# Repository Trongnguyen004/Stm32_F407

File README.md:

# Stm32_F407

### #Hình ảnh
<p align="center">
  <table>
    <tr>
      <td>
        
      </td>
      <td>
        
      </td>
    </tr>
  </table>
</p>

### #3D PCB

<p align="center">
  <table>
    <tr>
      <td>
        
      </td>
      <td>
        
      </td>
    </tr>
  </table>
</p>

### #Layout

### #Schematic

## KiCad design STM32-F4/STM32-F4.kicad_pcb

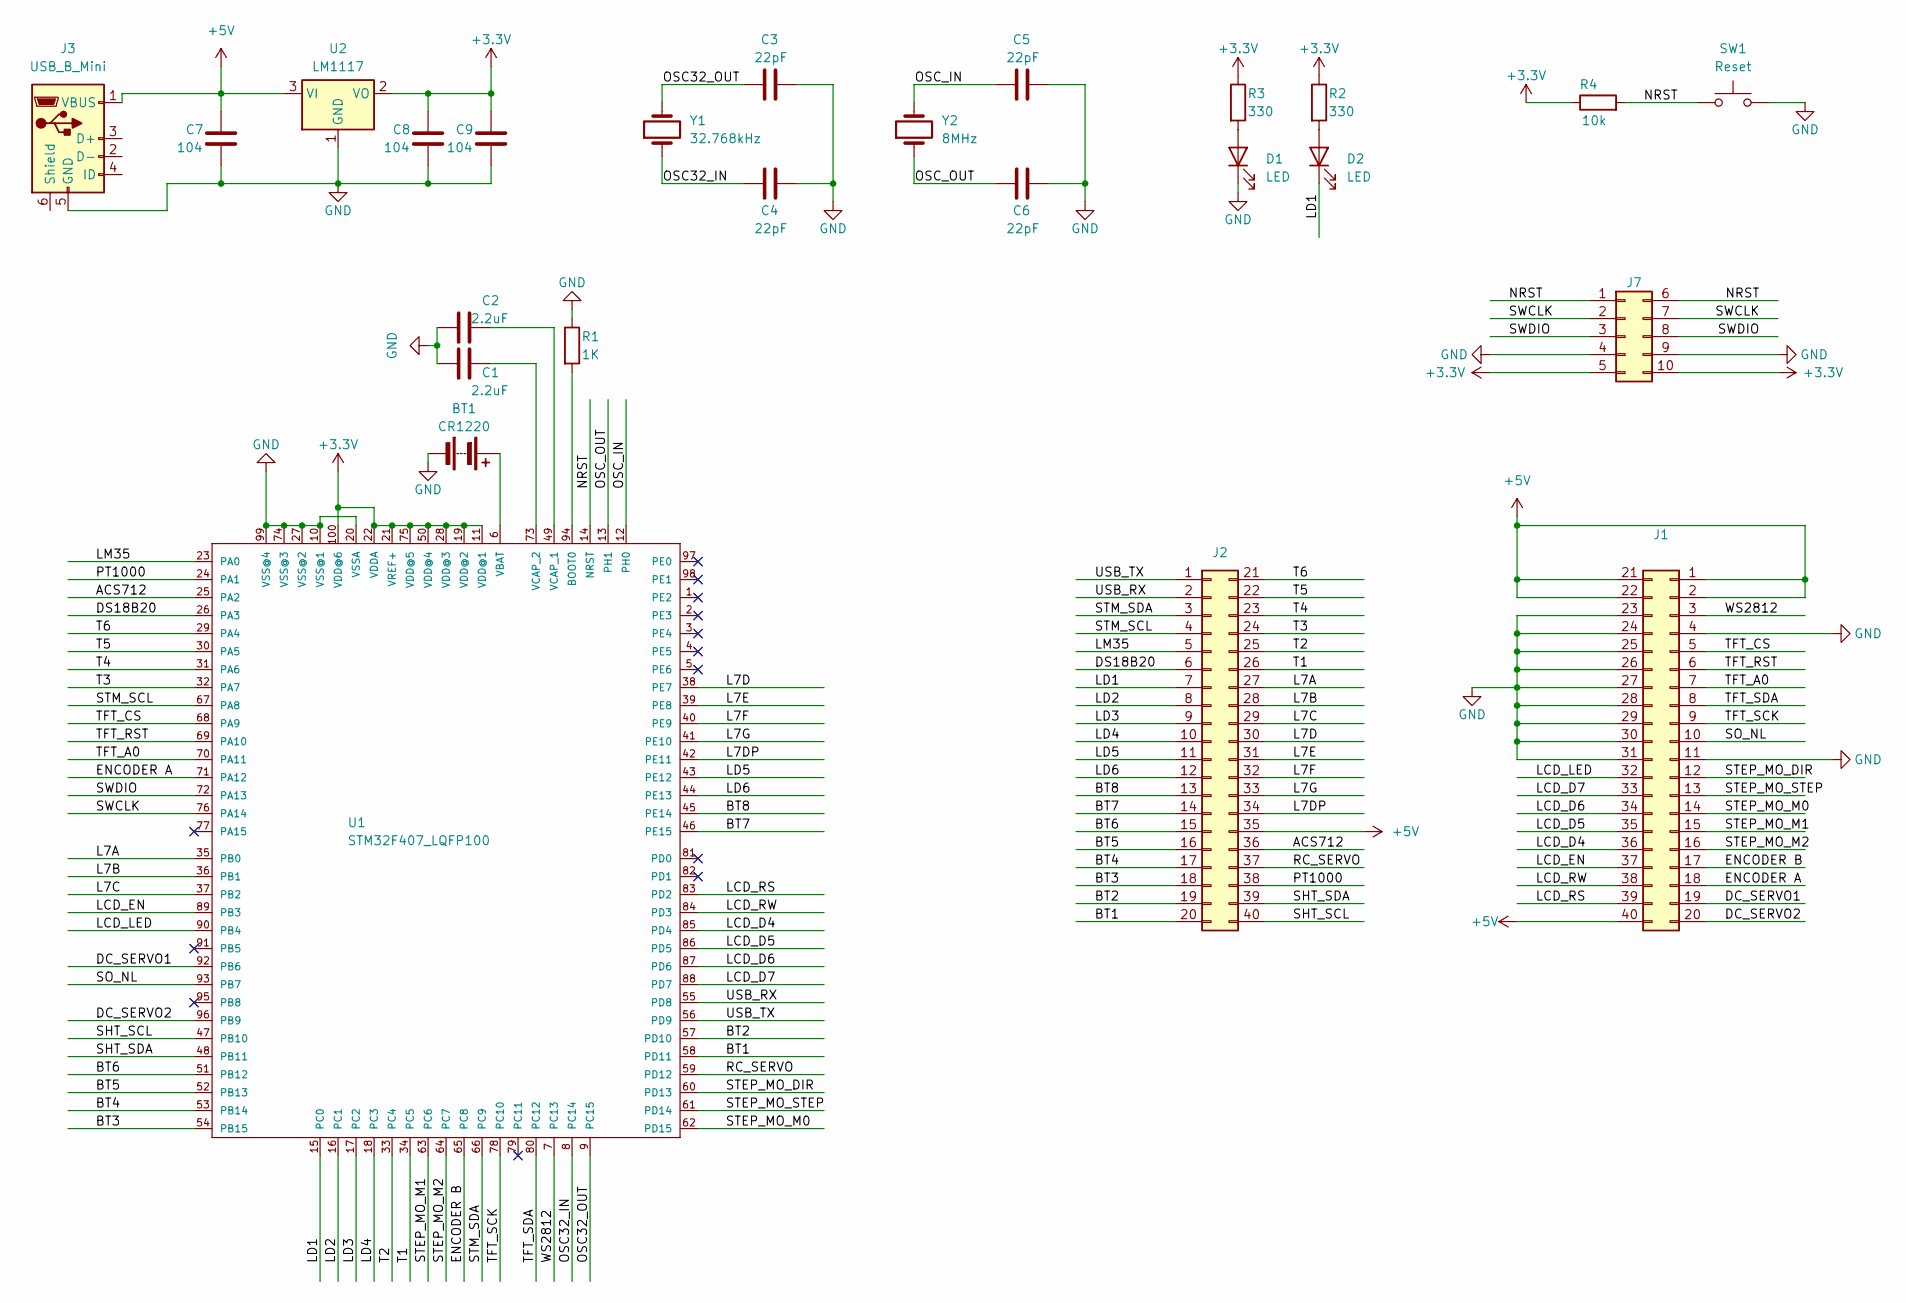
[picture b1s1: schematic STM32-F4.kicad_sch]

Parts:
BT1: CR1220; MPD_BC501SM-TR
C1, C2: 2.2uF; C_0805_2012Metric
C3, C4, C5, C6: 22pF; C_0805_2012Metric
C7, C8, C9: 104; C_0805_2012Metric
D1, D2: LED; LED_0805_2012Metric_Pad1.15x1.40mm_HandSolder
J1, J2: PinHeader_2x20_P2.54mm_Vertical
J3: USB_B_Mini; USB_Mini-B_Wuerth_65100516121_Horizontal
J7: PinHeader_2x05_P2.54mm_Vertical
R1: 1K; R_0805_2012Metric
R2, R3: 330; R_0805_2012Metric
R4: 10k; R_0805_2012Metric
SW1: Reset; SW_PUSH_6mm
U1: STM32F407_LQFP100; LQFP100-0.5-13.8X13.8MM; MPN STM32F407VET6
U2: LM1117; SOT-223-3_TabPin2
Y1: 32.768kHz; XTAL_AB38T-32.768KHZ
Y2: 8MHz; Crystal_HC49-4H_Vertical

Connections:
+3.3V: C8.1, C9.1, J7.5, J7.10, R2.1, R3.1, R4.1, U1.11 (VDD@1), U1.19 (VDD@2), U1.21 (VREF+), U1.22 (VDDA), U1.28 (VDD@3), U1.50 (VDD@4), U1.75 (VDD@5), U1.100 (VDD@6), U2.2 (VO)
+5V: C7.1, J1.1, J1.2, J1.21, J1.22, J1.40, J2.35, J3.1 (VBUS), U2.3 (VI)
/ACS712: J2.36, U1.25 (PA2)
/BT1: J2.20, U1.58 (PD11)
/BT2: J2.19, U1.57 (PD10)
/BT3: J2.18, U1.54 (PB15)
/BT4: J2.17, U1.53 (PB14)
/BT5: J2.16, U1.52 (PB13)
/BT6: J2.15, U1.51 (PB12)
/BT7: J2.14, U1.46 (PE15)
/BT8: J2.13, U1.45 (PE14)
/DC_SERVO1: J1.19, U1.92 (PB6)
/DC_SERVO2: J1.20, U1.96 (PB9)
/DS18B20: J2.6, U1.26 (PA3)
/ENCODER A: J1.18, U1.71 (PA12)
/ENCODER B: J1.17, U1.65 (PC8)
/L7A: J2.27, U1.35 (PB0)
/L7B: J2.28, U1.36 (PB1)
/L7C: J2.29, U1.37 (PB2)
/L7D: J2.30, U1.38 (PE7)
/L7DP: J2.34, U1.42 (PE11)
/L7E: J2.31, U1.39 (PE8)
/L7F: J2.32, U1.40 (PE9)
/L7G: J2.33, U1.41 (PE10)
/LCD_D4: J1.36, U1.85 (PD4)
/LCD_D5: J1.35, U1.86 (PD5)
/LCD_D6: J1.34, U1.87 (PD6)
/LCD_D7: J1.33, U1.88 (PD7)
/LCD_EN: J1.37, U1.89 (PB3)
/LCD_LED: J1.32, U1.90 (PB4)
/LCD_RS: J1.39, U1.83 (PD2)
/LCD_RW: J1.38, U1.84 (PD3)
/LD1: D2.1 (K), J2.7, U1.15 (PC0)
/LD2: J2.8, U1.16 (PC1)
/LD3: J2.9, U1.17 (PC2)
/LD4: J2.10, U1.18 (PC3)
/LD5: J2.11, U1.43 (PE12)
/LD6: J2.12, U1.44 (PE13)
/LM35: J2.5, U1.23 (PA0)
/NRST: J7.1, J7.6, R4.2, SW1.1, U1.14 (NRST)
/OSC32_IN: C4.1, U1.8 (PC14), Y1.1
/OSC32_OUT: C3.1, U1.9 (PC15), Y1.2
/OSC_IN: C5.1, U1.12 (PH0), Y2.2
/OSC_OUT: C6.1, U1.13 (PH1), Y2.1
/PT1000: J2.38, U1.24 (PA1)
/RC_SERVO: J2.37, U1.59 (PD12)
/SHT_SCL: J2.40, U1.47 (PB10)
/SHT_SDA: J2.39, U1.48 (PB11)
/SO_NL: J1.10, U1.93 (PB7)
/STEP_MO_DIR: J1.12, U1.60 (PD13)
/STEP_MO_M0: J1.14, U1.62 (PD15)
/STEP_MO_M1: J1.15, U1.63 (PC6)
/STEP_MO_M2: J1.16, U1.64 (PC7)
/STEP_MO_STEP: J1.13, U1.61 (PD14)
/STM_SCL: J2.4, U1.67 (PA8)
/STM_SDA: J2.3, U1.66 (PC9)
/SWCLK: J7.2, J7.7, U1.76 (PA14)
/SWDIO: J7.3, J7.8, U1.72 (PA13)
/T1: J2.26, U1.34 (PC5)
/T2: J2.25, U1.33 (PC4)
/T3: J2.24, U1.32 (PA7)
/T4: J2.23, U1.31 (PA6)
/T5: J2.22, U1.30 (PA5)
/T6: J2.21, U1.29 (PA4)
/TFT_A0: J1.7, U1.70 (PA11)
/TFT_CS: J1.5, U1.68 (PA9)
/TFT_RST: J1.6, U1.69 (PA10)
/TFT_SCK: J1.9, U1.78 (PC10)
/TFT_SDA: J1.8, U1.80 (PC12)
/USB_RX: J2.2, U1.55 (PD8)
/USB_TX: J2.1, U1.56 (PD9)
/WS2812: J1.3, U1.7 (PC13)
GND: BT1.-, C1.1, C2.1, C3.2, C4.2, C5.2, C6.2, C7.2, C8.2, C9.2, D1.1 (K), J1.4, J1.11, J1.23, J1.24, J1.25, J1.26, J1.27, J1.28, J1.29, J1.30, J1.31, J3.5 (GND), J7.4, J7.9, R1.1, SW1.2, U1.10 (VSS@1), U1.20 (VSSA), U1.27 (VSS@2), U1.74 (VSS@3), U1.99 (VSS@4), U2.1 (GND)
unnamed: D1.2 (A), R3.2
unnamed: D2.2 (A), R2.2
unnamed: R1.2, U1.94 (BOOT0)
unnamed: BT1.+, U1.6 (VBAT)
unnamed: C2.2, U1.49 (VCAP_1)
unnamed: C1.2, U1.73 (VCAP_2)

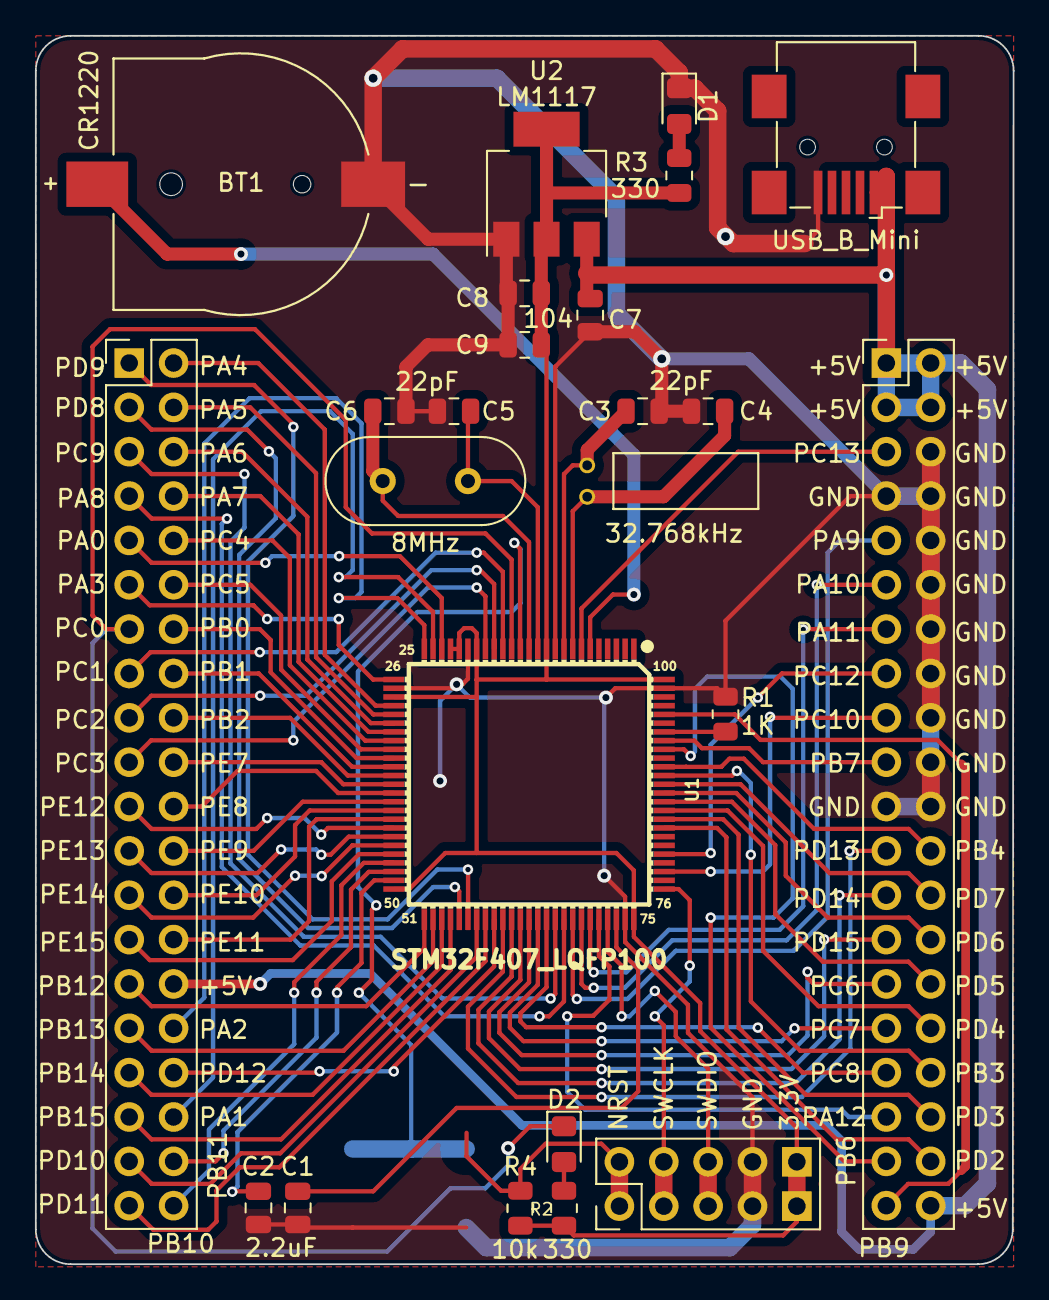
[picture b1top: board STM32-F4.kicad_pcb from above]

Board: 2 copper layers, 56.0 x 70.3 mm, 24 parts (0 on the bottom side), 79 nets.
